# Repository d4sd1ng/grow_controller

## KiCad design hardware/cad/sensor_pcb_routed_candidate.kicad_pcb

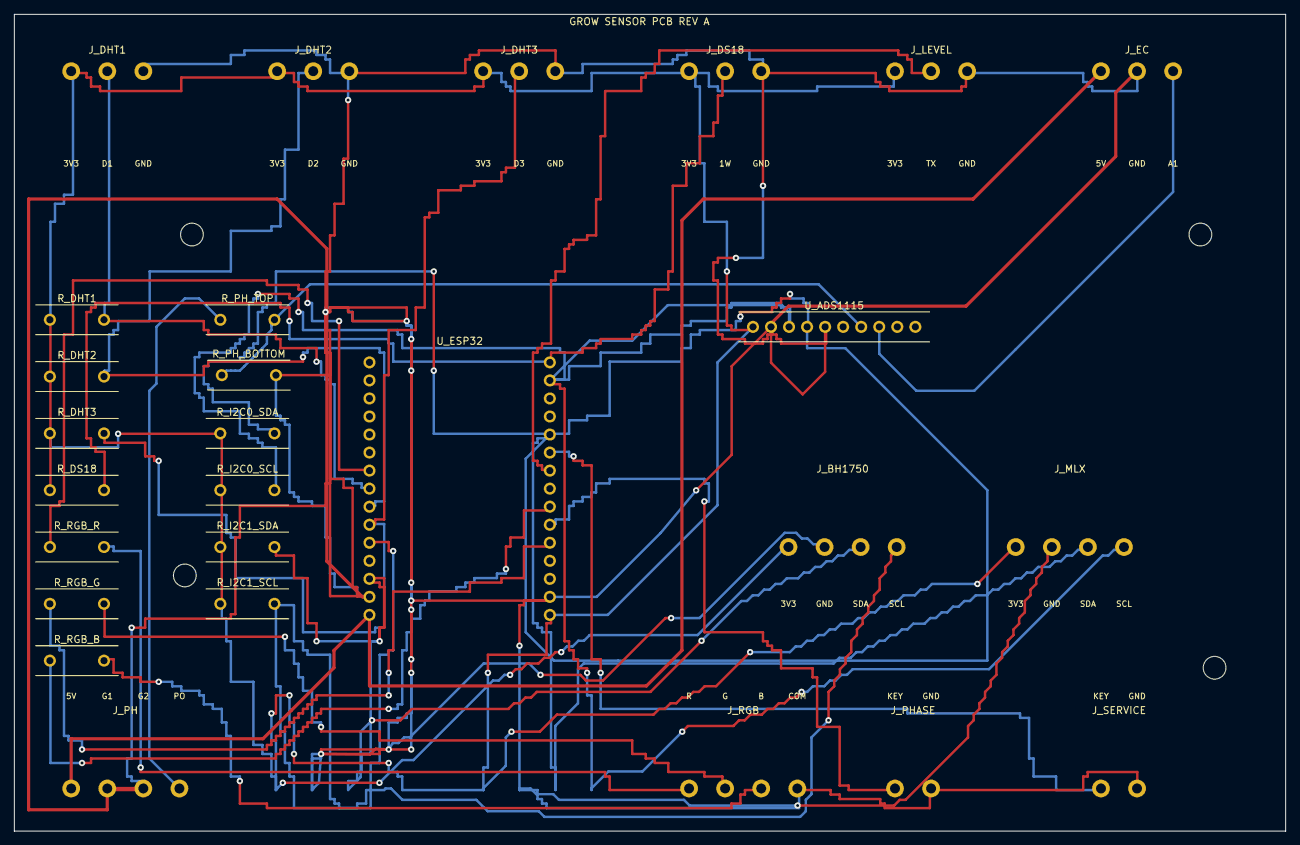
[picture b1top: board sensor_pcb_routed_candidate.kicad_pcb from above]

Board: 2 copper layers, 179.0 x 115.0 mm, 31 parts (0 on the bottom side), 23 nets.

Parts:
H1, H2, H3, H4: MountingHole_3.2mm_M3; MountingHole_3p2_M3
J_BH1750: Phoenix_1757268_MSTBA_4P; MSTBA_4P_5p08_to_NORTH
J_DHT1, J_DHT2, J_DHT3: Phoenix_1757255_MSTBA_3P; MSTBA_3P_5p08_to_SOUTH
J_DS18: Phoenix_1757255_MSTBA_3P; MSTBA_3P_5p08_to_SOUTH
J_EC: Phoenix_1757255_MSTBA_3P; MSTBA_3P_5p08_to_SOUTH
J_LEVEL: Phoenix_1757255_MSTBA_3P; MSTBA_3P_5p08_to_SOUTH
J_MLX: Phoenix_1757268_MSTBA_4P; MSTBA_4P_5p08_to_NORTH
J_PH: Phoenix_1757268_MSTBA_4P; MSTBA_4P_5p08_to_NORTH
J_PHASE: Phoenix_1757242_MSTBA_2P; MSTBA_2P_5p08_to_NORTH
J_RGB: Phoenix_1757268_MSTBA_4P; MSTBA_4P_5p08_to_NORTH
J_SERVICE: Phoenix_1757242_MSTBA_2P; MSTBA_2P_5p08_to_NORTH
R_DHT1, R_DHT2, R_DHT3: Resistor_Axial_P7.62; Axial_THT_DIN0207_P7p62
R_DS18: Resistor_Axial_P7.62; Axial_THT_DIN0207_P7p62
R_I2C0_SCL, R_I2C0_SDA, R_I2C1_SCL, R_I2C1_SDA: Resistor_Axial_P7.62; Axial_THT_DIN0207_P7p62
R_PH_BOTTOM: 20k; Axial_THT_DIN0207_P7p62
R_PH_TOP: 10k; Axial_THT_DIN0207_P7p62
R_RGB_B: Resistor_Axial_P7.62; Axial_THT_DIN0207_P7p62
R_RGB_G: Resistor_Axial_P7.62; Axial_THT_DIN0207_P7p62
R_RGB_R: Resistor_Axial_P7.62; Axial_THT_DIN0207_P7p62
U_ADS1115: ADS1115_10Pin_P2.54; ADS1115_Module_1x10_P2p54
U_ESP32: ESP32_30Pin_28x51mm; ESP32_30Pin_25p40_28x51

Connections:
3V3: J_BH1750.1, J_DHT1.1, J_DHT2.1, J_DHT3.1, J_DS18.1, J_LEVEL.1, J_MLX.1, R_DHT1.1, R_DHT2.1, R_DHT3.1, R_DS18.1, R_I2C0_SCL.1, R_I2C0_SDA.1, R_I2C1_SCL.1, R_I2C1_SDA.1, U_ADS1115.1, U_ESP32.16
5V_USB_BOARD: J_EC.1, J_PH.1, U_ESP32.15
DHT1_DATA: J_DHT1.2, R_DHT1.2, U_ESP32.8
DHT2_DATA: J_DHT2.2, R_DHT2.2, U_ESP32.9
DHT3_DATA: J_DHT3.2, R_DHT3.2, U_ESP32.10
DS18_DATA: J_DS18.2, R_DS18.2, U_ESP32.30
EC_ANALOG_UNVERIFIED: J_EC.3, U_ADS1115.8
GND: J_BH1750.2, J_DHT1.3, J_DHT2.3, J_DHT3.3, J_DS18.3, J_EC.2, J_LEVEL.3, J_MLX.2, J_PH.2, J_PH.3, J_PHASE.2, J_RGB.4, J_SERVICE.2, R_PH_BOTTOM.2, U_ADS1115.2, U_ADS1115.5, U_ESP32.14, U_ESP32.17
I2C_BH_SCL: J_BH1750.4, R_I2C1_SCL.2, U_ESP32.11
I2C_BH_SDA: J_BH1750.3, R_I2C1_SDA.2, U_ESP32.13
I2C_MAIN_SCL: J_MLX.4, R_I2C0_SCL.2, U_ADS1115.3, U_ESP32.29
I2C_MAIN_SDA: J_MLX.3, R_I2C0_SDA.2, U_ADS1115.4, U_ESP32.26
LEVEL_TX: J_LEVEL.2, U_ESP32.24
PHASE_BUTTON: J_PHASE.1, U_ESP32.21
PH_A0_CONDITIONED_UNVERIFIED: R_PH_BOTTOM.1, R_PH_TOP.2, U_ADS1115.7
PH_PO_UNVERIFIED: J_PH.4, R_PH_TOP.1
RGB_B_GPIO: R_RGB_B.1, U_ESP32.22
RGB_B_LED: J_RGB.3, R_RGB_B.2
RGB_G_GPIO: R_RGB_G.1, U_ESP32.20
RGB_G_LED: J_RGB.2, R_RGB_G.2
RGB_R_GPIO: R_RGB_R.1, U_ESP32.7
RGB_R_LED: J_RGB.1, R_RGB_R.2
SERVICE_BUTTON: J_SERVICE.1, U_ESP32.25

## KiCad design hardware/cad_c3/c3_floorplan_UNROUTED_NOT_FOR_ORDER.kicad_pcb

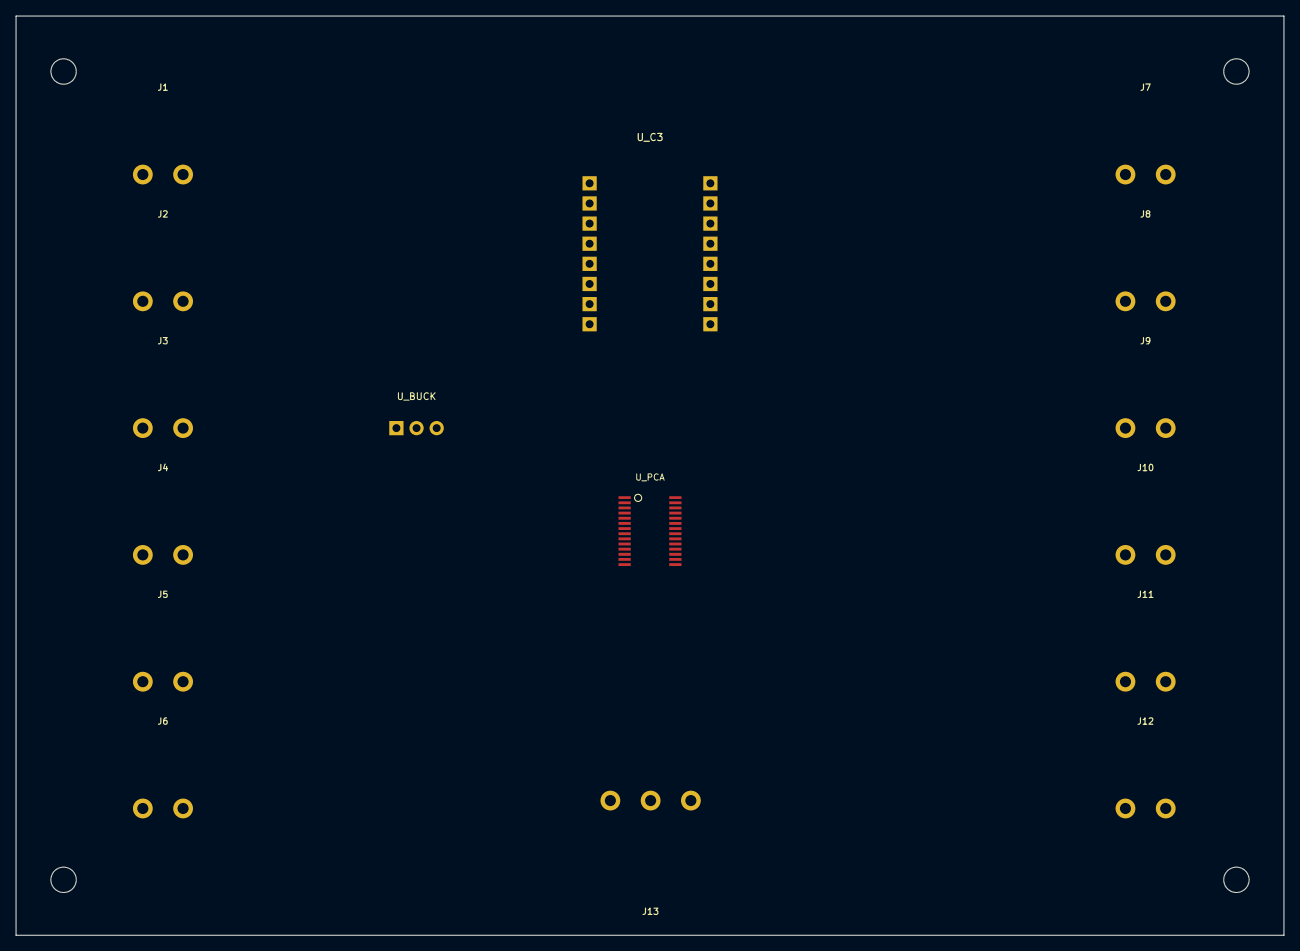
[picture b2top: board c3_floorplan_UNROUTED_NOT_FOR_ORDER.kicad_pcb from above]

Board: 2 copper layers, 160.0 x 116.0 mm, 20 parts (0 on the bottom side), 3 nets, no tracks yet.

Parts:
H1, H2, H3, H4: M3; MountingHole_3p2_M3
J1, J2, J3, J4, J5, J6, J7, J8, J9, J10, J11, J12: PHOENIX_1757242; MSTBA_2P_5p08_NORTH
J13: PHOENIX_1757255; MSTBA_3P_5p08_SOUTH
U_BUCK: R-78E5.0-1.0; RECOM_R-78E5.0-1.0_SIP3
U_C3: ESP32-C3 SUPERMINI; ESP32_C3_SuperMini_2x8_15p24
U_PCA: PCA9685PW; PCA9685PW_TSSOP28_4p4x9p7

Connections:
+5V_BUCK_UNROUTED: U_BUCK.3, U_C3.1
+12V_IN_UNROUTED: J1.1, U_BUCK.1
GND_UNROUTED: J1.2, U_BUCK.2, U_C3.2

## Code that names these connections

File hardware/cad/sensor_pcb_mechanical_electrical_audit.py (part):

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                  "GND", "ALRT_NC", "PH_A0_CONDITIONED_UNVERIFIED",
                  "EC_ANALOG_UNVERIFIED", "A2_NC", "A3_NC"],
    "U_ESP32": ["EN", "GPIO36_NC", "GPIO39_NC", "GPIO34_NC",
                "GPIO35_NC", "GPIO32_NC", "RGB_R_GPIO",
                "DHT1_DATA", "DHT2_DATA", "DHT3_DATA",
                "I2C_BH_SCL", "GPIO12_NC", "I2C_BH_SDA",
                "GND", "5V_USB_BOARD", "3V3", "GND",
                "GPIO15_NC", "GPIO2_NC", "RGB_G_GPIO",
                "PHASE_BUTTON", "RGB_B_GPIO", "GPIO5_NC",
                "LEVEL_TX", "SERVICE_BUTTON", "I2C_MAIN_SDA",
                "GPIO3_NC", "GPIO1_NC", "I2C_MAIN_SCL",
                "DS18_DATA"],
}
expected["R_PH_TOP"] = ["PH_PO_UNVERIFIED", "PH_A0_CONDITIONED_UNVERIFIED"]
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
